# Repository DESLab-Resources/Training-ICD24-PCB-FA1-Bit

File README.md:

# PCB of Full Adder 1-bit

Board Version 1.0: [FA 1-bit V1.0](https://github.com/DESLab-Resources/Training-ICD24-PCB-FA1-Bit/releases/tag/V1.0).

Other option from [Mr. Hoang Trinh @thhq](https://github.com/DESLab-Resources/Training-ICD24-PCB-FA1-Bit/tree/thh_branch).

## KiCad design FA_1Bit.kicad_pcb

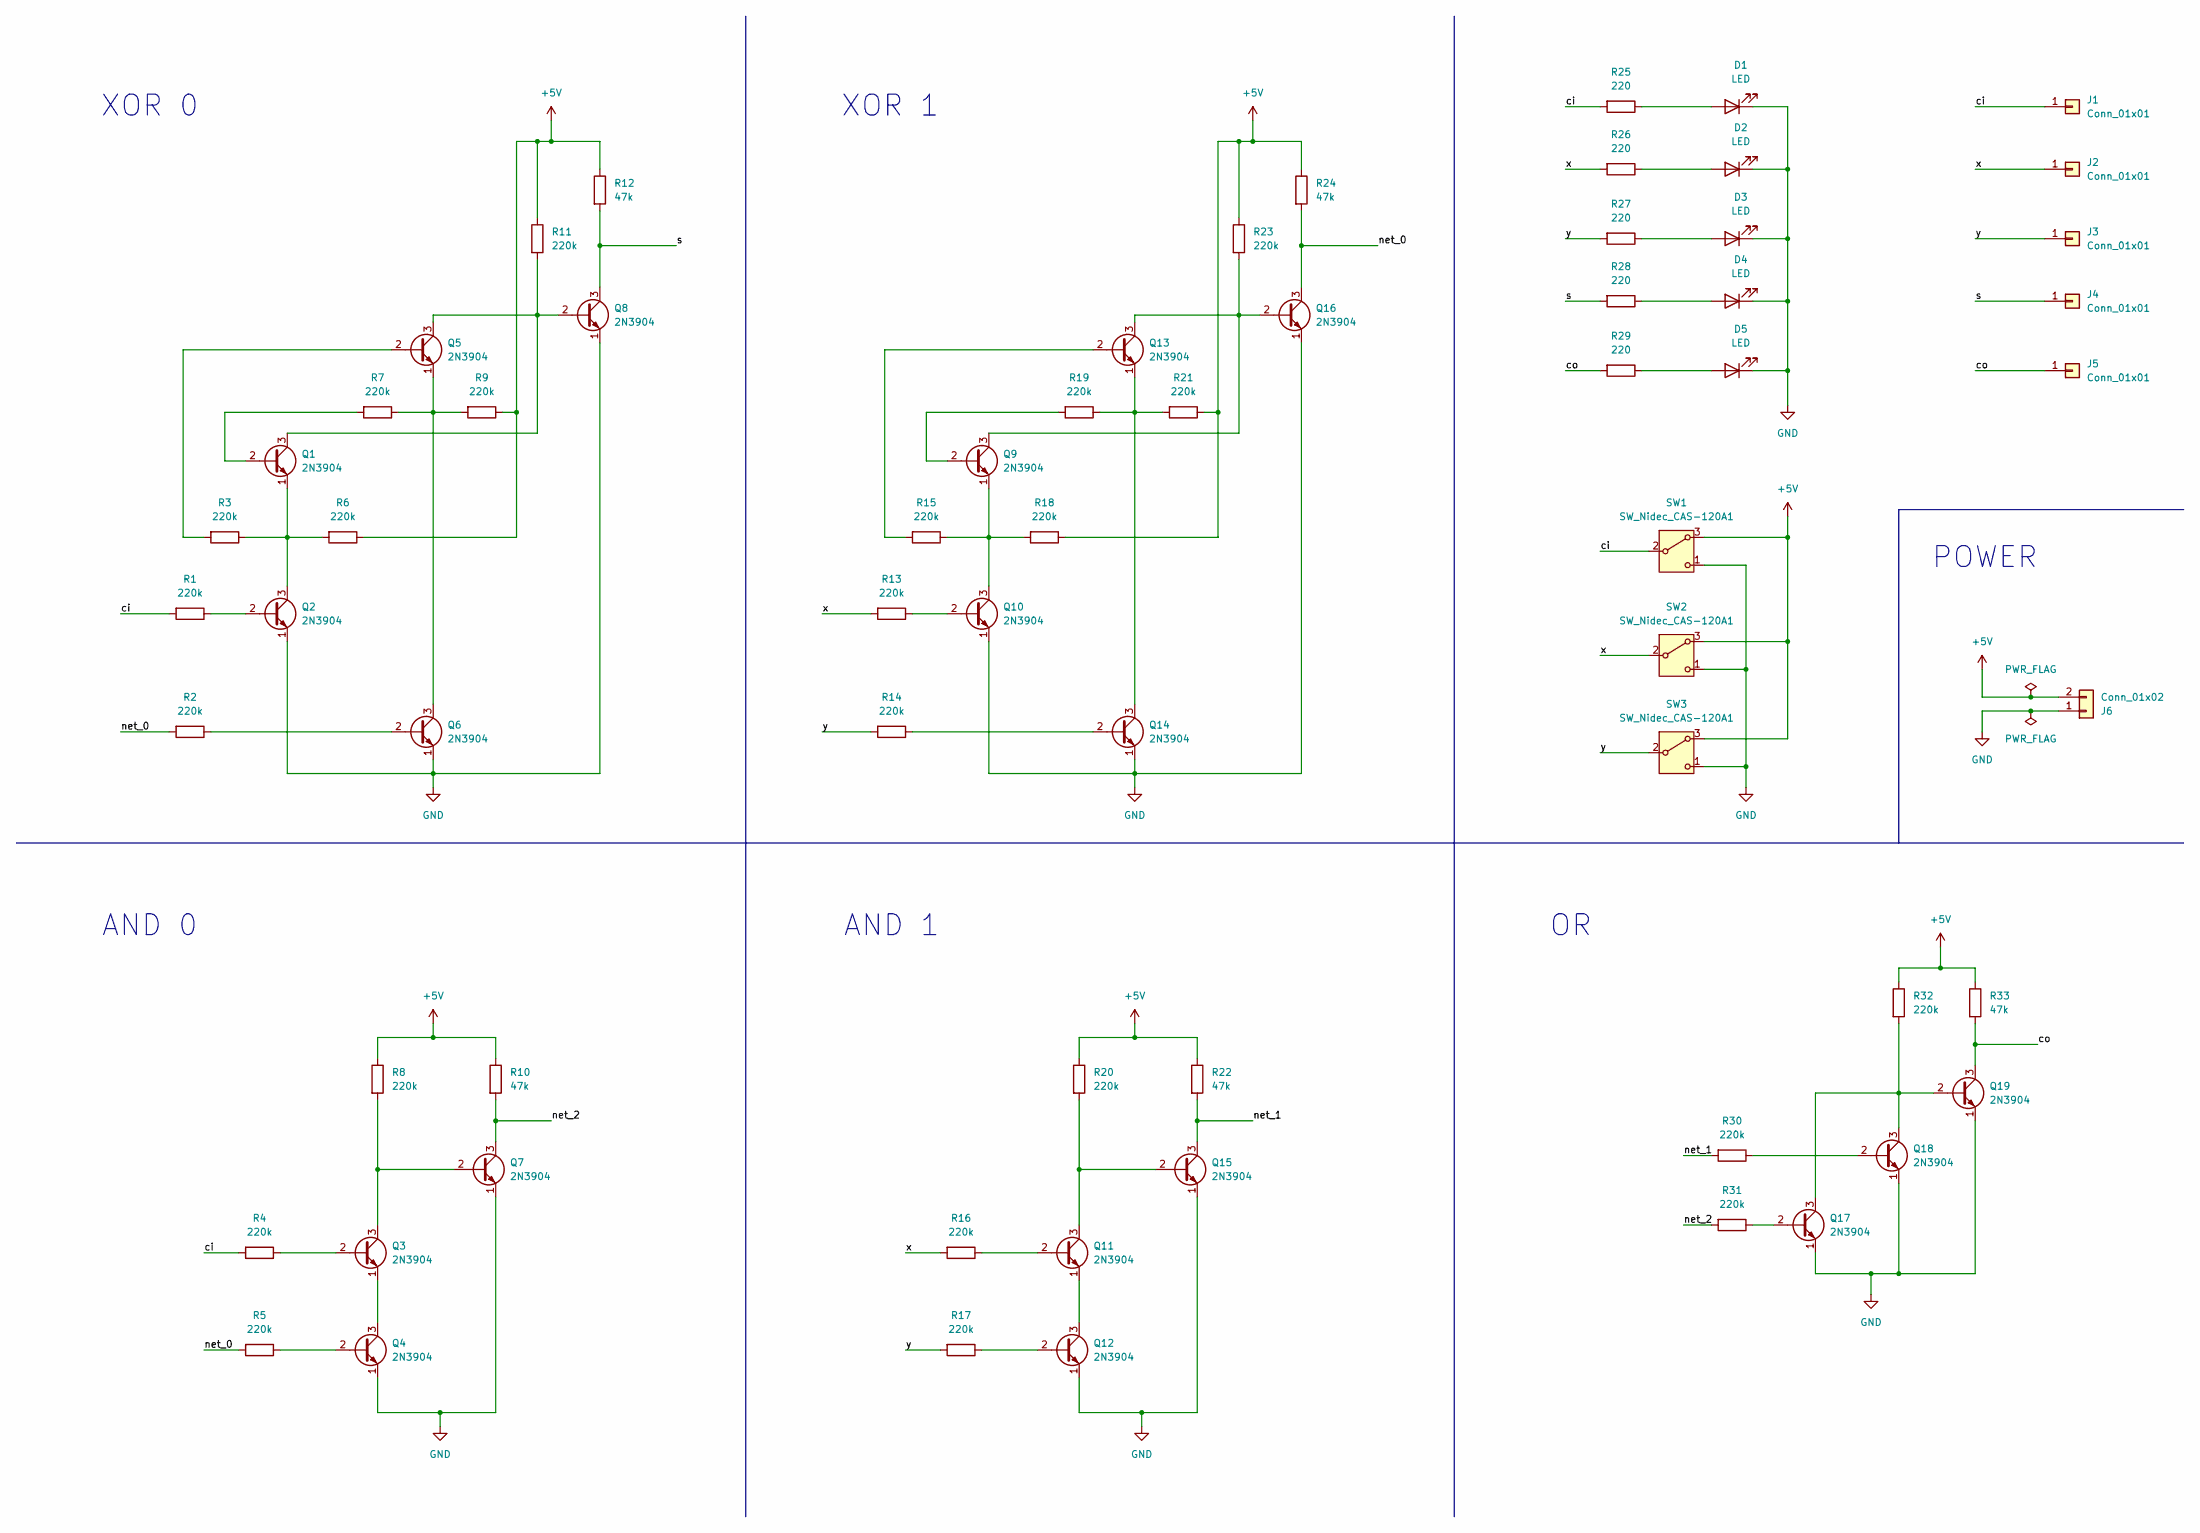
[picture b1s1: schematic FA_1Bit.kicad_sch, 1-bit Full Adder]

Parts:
D1, D2, D3, D4, D5: LED; LED_D3.0mm
J1, J2, J3, J4, J5: Conn_01x01; PinHeader_1x01_P2.54mm_Horizontal
J6: Conn_01x02; TerminalBlock_Phoenix_MPT-0,5-2-2.54_1x02_P2.54mm_Horizontal
Q1, Q2, Q3, Q4, Q5, Q6, Q7, Q8, Q9, Q10, Q11, Q12, Q13, Q14, Q15, Q16, Q17, Q18, Q19: 2N3904; TO-92_Inline
R1, R2, R3, R4, R5, R6, R7, R8, R9, R11, R13, R14, R15, R16, R17, R18, R19, R20, R21, R23, R30, R31, R32: 220k; R_Axial_DIN0204_L3.6mm_D1.6mm_P5.08mm_Horizontal
R10, R12, R22, R24, R33: 47k; R_Axial_DIN0204_L3.6mm_D1.6mm_P5.08mm_Horizontal
R25, R26, R27, R28, R29: 220; R_Axial_DIN0204_L3.6mm_D1.6mm_P5.08mm_Horizontal
SW1, SW2, SW3: SW_Nidec_CAS-120A1; SW_SS12D07VG4

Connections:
+5V: J6.2, R6.1, R8.1, R9.1, R10.1, R11.1, R12.1, R18.1, R20.1, R21.1, R22.1, R23.1, R24.1, R32.1, R33.1, SW1.3 (A), SW2.3 (A), SW3.3 (A)
/ci: J1.1, R1.2, R4.2, R25.2, SW1.2 (B)
/co: J5.1, Q19.3 (C), R29.2, R33.2
/net_0: Q16.3 (C), R2.2, R5.2, R24.2
/net_1: Q15.3 (C), R22.2, R30.2
/net_2: Q7.3 (C), R10.2, R31.2
/s: J4.1, Q8.3 (C), R12.2, R28.2
/x: J2.1, R13.2, R16.2, R26.2, SW2.2 (B)
/y: J3.1, R14.2, R17.2, R27.2, SW3.2 (B)
GND: D1.1 (K), D2.1 (K), D3.1 (K), D4.1 (K), D5.1 (K), J6.1, Q2.1 (E), Q4.1 (E), Q6.1 (E), Q7.1 (E), Q8.1 (E), Q10.1 (E), Q12.1 (E), Q14.1 (E), Q15.1 (E), Q16.1 (E), Q17.1 (E), Q18.1 (E), Q19.1 (E), SW1.1 (C), SW2.1 (C), SW3.1 (C)
unnamed: D1.2 (A), R25.1
unnamed: D2.2 (A), R26.1
unnamed: D3.2 (A), R27.1
unnamed: D4.2 (A), R28.1
unnamed: D5.2 (A), R29.1
unnamed: Q1.2 (B), R7.2
unnamed: Q1.3 (C), Q5.3 (C), Q8.2 (B), R11.2
unnamed: Q1.1 (E), Q2.3 (C), R3.1, R6.2
unnamed: Q2.2 (B), R1.1
unnamed: Q3.2 (B), R4.1
unnamed: Q3.3 (C), Q7.2 (B), R8.2
unnamed: Q3.1 (E), Q4.3 (C)
unnamed: Q4.2 (B), R5.1
unnamed: Q5.2 (B), R3.2
unnamed: Q5.1 (E), Q6.3 (C), R7.1, R9.2
unnamed: Q6.2 (B), R2.1
unnamed: Q9.2 (B), R19.2
unnamed: Q10.2 (B), R13.1
unnamed: Q9.1 (E), Q10.3 (C), R15.1, R18.2
unnamed: Q11.2 (B), R16.1
unnamed: Q11.3 (C), Q15.2 (B), R20.2
unnamed: Q11.1 (E), Q12.3 (C)
unnamed: Q12.2 (B), R17.1
unnamed: Q13.2 (B), R15.2
unnamed: Q9.3 (C), Q13.3 (C), Q16.2 (B), R23.2
unnamed: Q13.1 (E), Q14.3 (C), R19.1, R21.2
unnamed: Q14.2 (B), R14.1
unnamed: Q17.2 (B), R31.1
unnamed: Q17.3 (C), Q18.3 (C), Q19.2 (B), R32.2
unnamed: Q18.2 (B), R30.1

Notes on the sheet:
XOR 0
XOR 1
AND 0
POWER
AND 1

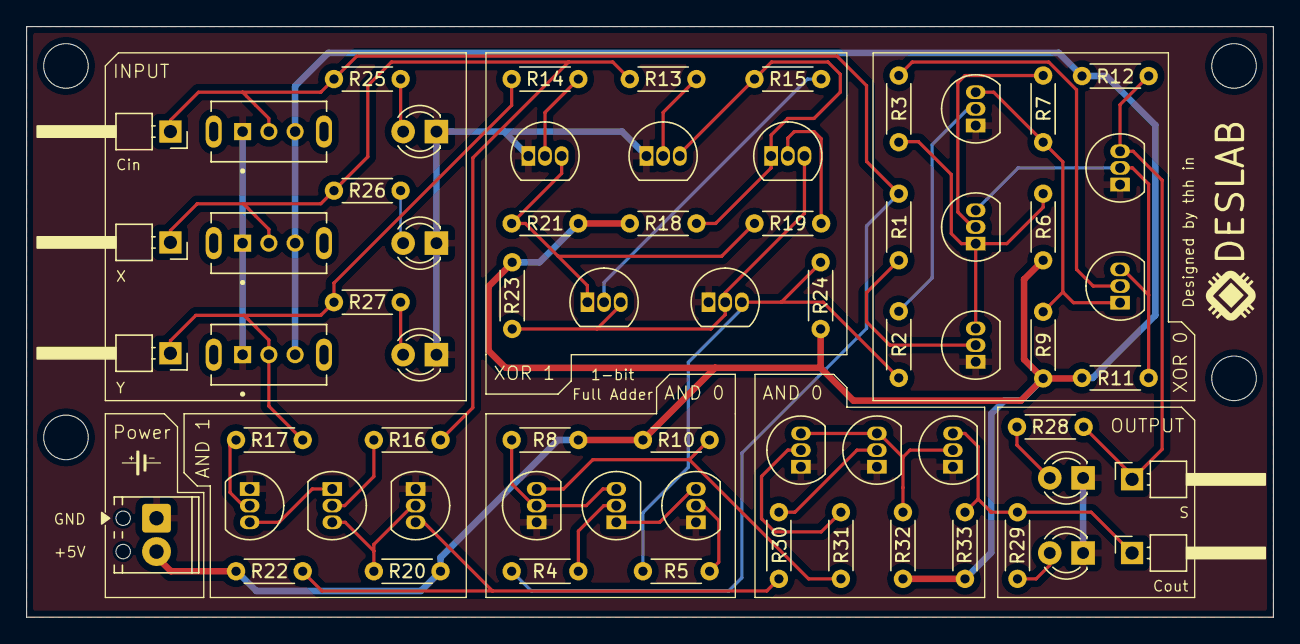
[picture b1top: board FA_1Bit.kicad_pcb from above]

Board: 2 copper layers, 95.0 x 45.0 mm, 66 parts (0 on the bottom side), 40 nets.

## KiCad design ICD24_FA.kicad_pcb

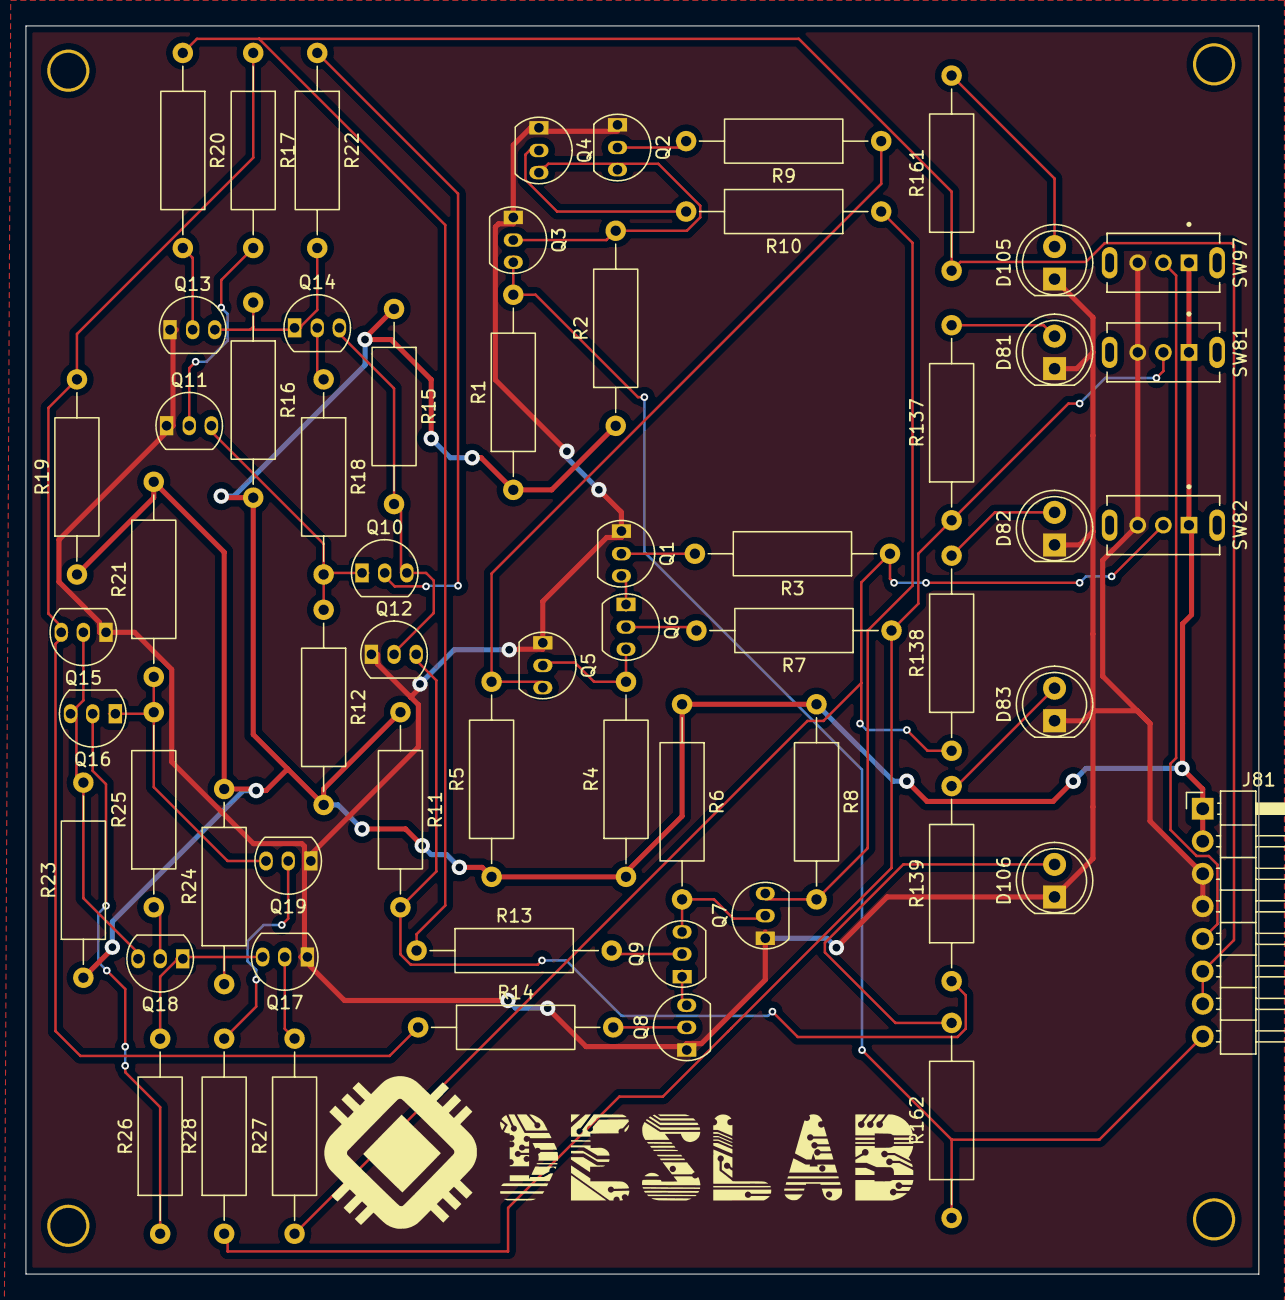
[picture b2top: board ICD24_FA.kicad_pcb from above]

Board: 2 copper layers, 96.3 x 97.5 mm, 65 parts (0 on the bottom side), 41 nets.

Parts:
D81, D82, D83, D105, D106: LED; LED_D5.0mm
J81: Conn_01x08; PinHeader_1x08_P2.54mm_Horizontal
Q1, Q2, Q3, Q4, Q5, Q6, Q7, Q8, Q9, Q10, Q11, Q12, Q13, Q14, Q15, Q16, Q17, Q18, Q19: 2N3904; TO-92_Inline
R1, R5, R8, R11, R19, R137, R138, R139, R161, R162: 47k; R_Axial_DIN0309_L9.0mm_D3.2mm_P15.24mm_Horizontal
R2, R3, R4, R6, R7, R9, R10, R12, R13, R14, R15, R16, R17, R18, R20#5, R21, R22, R23, R24, R25, R26, R27, R28: 220k; R_Axial_DIN0309_L9.0mm_D3.2mm_P15.24mm_Horizontal
R20, R20#2, R20#3, R20#4: 220k; MyPAD
SW81, SW82, SW97: SW_SPDT; SW_SS12D07VG4

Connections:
0: D81.1 (K), D82.1 (K), D83.1 (K), D105.1 (K), D106.1 (K), J81.3, J81.4, Q1.1 (E), Q2.1 (E), Q3.1 (E), Q4.1 (E), Q5.1 (E), Q7.1 (E), Q8.1 (E), Q11.1 (E), Q12.1 (E), Q13.1 (E), Q15.1 (E), Q17.1 (E), Q19.1 (E), SW81.3 (C), SW82.3 (C), SW97.3 (C)
/fa1_bit/fa1/and_gate1/OUT: Q5.3 (C), R5.2, R9.1
/fa1_bit/fa1/and_gate/IN_B: Q15.3 (C), R14.1, R17.1, R19.2
/fa1_bit/fa1/and_gate/OUT: Q7.3 (C), R8.2, R10.1
CIN: J81.6, J81.7, R13.1, R20#5.1, R161.1
CIN_Port: J81.5, SW97.2 (B)
IN_A0: R7.1, R28.1, R137.1, SW81.2 (B)
IN_B0: R3.1, R27.1, R138.1, SW82.2 (B)
unnamed: D81.2 (A), R137.2
unnamed: D82.2 (A), R138.2
unnamed: D83.2 (A), R139.2
unnamed: D105.2 (A), R161.2
unnamed: D106.2 (A), R162.2
unnamed: Q1.2 (B), R3.2
unnamed: Q1.3 (C), Q6.1 (E)
unnamed: Q2.2 (B), R9.2
unnamed: Q2.3 (C), Q3.2 (B), Q4.3 (C), R2.2
unnamed: Q4.2 (B), R10.2
unnamed: Q5.2 (B), Q6.3 (C), R4.2
unnamed: Q6.2 (B), R7.2
unnamed: Q7.2 (B), Q9.3 (C), R6.2
unnamed: Q8.2 (B), R14.2
unnamed: Q8.3 (C), Q9.1 (E)
unnamed: Q9.2 (B), R13.2
unnamed: Q10.2 (B), R22.1
unnamed: Q10.3 (C), Q12.2 (B), Q14.3 (C), R15.2
unnamed: Q10.1 (E), Q11.3 (C), R12.1, R18.2
unnamed: Q11.2 (B), R17.2
unnamed: Q13.2 (B), R20#5.2
unnamed: Q13.3 (C), Q14.1 (E), R16.1, R22.2
unnamed: Q14.2 (B), R18.1
unnamed: Q15.2 (B), Q16.3 (C), Q18.3 (C), R23.2
unnamed: Q16.2 (B), R26.1
unnamed: Q16.1 (E), Q19.3 (C), R21.1, R25.2
unnamed: Q17.2 (B), R27.2
unnamed: Q17.3 (C), Q18.1 (E), R24.1, R26.2
unnamed: Q18.2 (B), R25.1
unnamed: Q19.2 (B), R28.2
OUT_COUT: J81.8, Q3.3 (C), R1.2, R162.1
OUT_SUM0: Q12.3 (C), R11.2, R139.1
VDD: J81.1, J81.2, R1.1, R2.1, R4.1, R5.1, R6.1, R8.1, R11.1, R12.2, R15.1, R16.2, R19.1, R21.2, R23.1, R24.2, SW81.1 (A), SW82.1 (A), SW97.1 (A)

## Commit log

2025-12-03 Init
2025-12-04 full, no layout
2025-12-06 FA 2-bit
2025-12-06 FA8 full sim, before FA1 layout
2025-12-07 FA 1-Bit PCB ok
2025-12-07 PCB with interconnections
2025-12-12 BOM and Picture
2025-12-12 temp
2025-12-12 Update link to Mr. Hoang Trinh's repository
2025-12-13 Update README with board version and options
    Added board version link and alternative option.
2025-12-13 Add additional reference to Mr. Hoang Trinh
